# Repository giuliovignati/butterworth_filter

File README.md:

🧈 **Butterworth Low-Pass Filter Design**
 
---

## 📘 Introduction

A **Butterworth filter** is a type of signal processing filter designed to have a frequency response that is as flat as mathematically possible in the passband. Unlike filters that exhibit ripples or irregularities in the passband or stopband, the Butterworth filter provides a smooth and monotonic response, making it ideal for applications that require minimal signal distortion.

This project focuses on the design and analysis of a 7th-order Butterworth low-pass filter based on specific performance requirements, including passband and stopband frequencies, maximum ripple, and minimum attenuation.

---

## 📐 Project Specifications

The specifications provided for this project are summarized in the following table:

| Filter Type |   $f_p$   |   $f_s$   |   $A_{\text{max}}$    |   $A_{\text{min}}$    |  $K$  |
|-------------|-----------|-----------|-----------------------|-----------------------|-------|
| Butterworth | 40 kHz    | 61 kHz    | 2 dB                  | 20 dB                 | 5     |

---

## 🔍 Parameter Calculation and Design Decisions

### 🎛️ Butterworth Filter Poles

The magnitude of the transfer function of a Butterworth filter $T(i\omega)$ is given by:

$|T(i\omega)| = \frac{1}{\sqrt{1 + \varepsilon^2 \left(\frac{\omega}{\omega_p}\right)^{2N}}}$

Where:

- $N$ is the filter order  
- $\varepsilon = \sqrt{10^{A_{\text{max}}/10} - 1} = 0.765$

To ensure a minimum attenuation of $A_{\text{min}}$ in the stopband, the minimum order $N$ required is calculated as:

$A(\omega_s) = 10 \log\left(1 + \varepsilon^2 \left(\frac{\omega_s}{\omega_p}\right)^{2N}\right)$

Solving gives:

$N_{\text{min}} = 7$

Poles lie on a semicircle in the complex plane:

$R = \omega_p \cdot \left(\frac{1}{\varepsilon}\right)^{1/7} = 261.129 \cdot 10^3 \, \text{rad/s}$

**Complex Poles of the Filter:**

| Index       | Pole Expression (in terms of $R$)         |
|-------------|-------------------------------------------|
|  $p_{0,6}$  | $R \cdot (-0.22252 \pm i \cdot 0.97493)$  |
|  $p_{1,5}$  | $R \cdot (-0.62349 \pm i \cdot 0.078183)$ |
|  $p_{2,4}$  | $R \cdot (-0.90097 \pm i \cdot 0.43388)$  |
|    $p_3$    | $-R $                                     |

---

### 🎚️ Pole Frequencies and Quality Factors

Given $p_k = R \cdot (\sigma_k + i\omega_k)$, we derive:

- Resonant frequency:  
  $\omega_0 = R$

- Quality factor:  
  $Q = -\frac{1}{2\sigma}$

**Quality Factors:**

| Poles     | Quality Factor $Q$ |
|-----------|--------------------|
| $p_{0,6}$ | $2.2469$           |
| $p_{1,5}$ | $0.8019$           |
| $p_{2,4}$ | $0.5549$           |

---

## 🔧 Filter Design

### 🧠 Design Choices

The project design involved balancing trade-offs among performance, component count, and sensitivity. The implemented solution includes three smart Sallen-Key stages, a single integrator stage, and an inverting buffer.

An alternative solution aimed at minimizing component usage would have included three Sallen-Key filters, one RC filter, and a non-inverting amplifier stage. This approach would have saved one operational amplifier. However, it was ultimately discarded in favor of a fully active solution, which offers greater versatility and improved performance.

Given the relatively non-stringent specifications, a general-purpose operational amplifier was selected, specifically the *TL072* (and *TL071*).

### 🧩 Component Value Calculation

Following the model of the smart Sallen-Key filter (schematic shown in the following figure), the resistor and capacitor values for each stage are determined according to the following equations:

$\omega_0 = \frac{1}{R \sqrt{C_1 C_2}} \quad$ ; $\quad Q = \frac{1}{2} \sqrt{\frac{C_1}{C_2}}$

Considering the values of $Q$ and $\omega_0$ obtained, and choosing discrete resistor and capacitor values that best approximate the theoretical values, the following values were obtained:

| Component | S-K 1 | S-K 2 | S-K 3 |
| --- | --- | --- | --- |
| $R [k\Omega]$ | $5.1$ | $7.5$ | $7.5$ |
| $C_1 [pF]$ | $820$ | $820$ | $2.2 \cdot 10^3$ |
| $C_2 [pF]$ | $680$ | $330$ | $100$ |
| $Q$ | $0.5491$ | $0.7882$ | $2.3452$ |
| $\omega_0 [krad/s]$ | $262.6$ | $256.3$ | $284.3$ |

For the integrator stage (based on the schematic) the following formulas are used:

$$
\omega_0 = \frac{1}{R_2 C}, \quad K = \frac{R_2}{R_1}
$$

The chosen values are: $R_1 = 8.1k\Omega$,  $R_2' = 39k\Omega$,  $R_2'' = 2k\Omega$, and  $C' = C'' = 47pF$. 

For the inverting buffer, the resistor values are $R = 10k\Omega$. Given the simple DC gain specification, all amplification is handled in the single-pole stage. Therefore, it was the only stage where care was taken to use resistor series to closely approximate the ideal gain value, while the capacitor parallel configuration was used primarily for sizing purposes.

Finally, the order of the stages, from input to output, is: integrator, Sallen-Key smart filter with increasing $Q$, and inverting buffer.

An additional note on filter sizing: Initially, different sizing was planned, especially for the first and third Sallen-Key stages. However, upon testing the real filter's performance and considering the numerous non-idealities of the circuit on a breadboard (e.g., parasitic capacitance), the actual values differed significantly from the expected ones (cutting off at around $4kHz$ instead of the target). As a result, an alternative sizing was chosen to better meet the design specifications, aiming to use larger capacitors to reduce parasitic effects.

## Circuit Sensitivity

The sensitivity values across all stages of the circuit are shown in the tables below. It can be observed that, due to the smart Sallen-Key configuration for all two-pole stages, the circuit exhibits excellent sensitivity values, making it highly robust to variations in component values.

### Sallen-Key Stage Sensitivity

| Component | Sensitivity Value |
| --- | --- |
| $S^Q_R$ | 0 |
| $S^Q_{C_1}$ | 0.5 |
| $S^Q_{C_2}$ | -0.5 |
| $S^{\omega_0}_{\{R,C_1,C_2\}}$ | -0.5 |

### Integrator Stage Sensitivity

| Component | Sensitivity Value |
| --- | --- |
| $S^K_{R_1}$ | -1 |
| $S^K_{R_2}$ | 1 |
| $S^{\omega_0}_{\{R_2,C\}}$ | -1 |
| $S^{\omega_0}_{R_1}$ | 0 |

### Inverting Buffer Sensitivity

| Component | Sensitivity Value |
| --- | --- |
| $S^K_{R_1}$ | -1 |
| $S^K_{R_2}$ | 1 |

--- 

## ⚙️ Spice Simulations
#### Schematic used for Spice simulations

### Fourier Domain Analysis

The previous schematic was used to perform the following Montecarlo simulation with $5\%$ tolerance for resistors and $15\%$ tolerance for capacitors, while the values presented in the table below refer to the simulation with exact nominal values. The last row in the table shows the actual frequency at which $A_{min} = 2dB$ is satisfied, which occurs with a $0.5kHz$ offset.

At this point, it is essential to observe that at $61kHz$, the attenuation is much smaller compared to the designed value ($\approx -6dB$). This discrepancy is due to the effect of additional poles in the circuit, probably caused by the non-idealities of the operational amplifiers. This effect can be directly observed in the simulation with nominal values by evaluating the phase Bode plot. In addition to the contribution from the 7 poles coinciding around $40kHz$, which would lead to a total phase shift of $630^\circ$, an additional phase shift is visible beyond $0.5MHz$, suggesting the presence of extra poles. It is worth noting that this behavior could have allowed us to achieve a solution that fully met the design specifications, for example, by simply shifting the cutoff frequency $\omega_0$ of the stages further ahead. However, we chose not to implement this solution in order to remain consistent with the theoretical models, while still obtaining valid results with this configuration.

#### Bode Diagram Simulation Values (Nominal Values)

| Frequency | $V_{out}/V_{in}$ [dB] | $V_{out}/V_{in}$ [V] |
| --- | --- | --- |
| $DC (1Hz)$ | $13.98$ | $5$ |
| $40kHz$ | $11.80$ | $3.89$ |
| $61kHz$ | $-8.67$ | $0.37$ |
| $39.5kHz$ | $11.98$ | $3.97$ |

#### Montecarlo simulation:

#### Montecarlo simulation with cutoff zoom:

#### Nominal frequency analysis:

### 🕒 Time Domain Analysis

The time domain simulations of the filter at the relevant frequencies are shown in the following graphs. The peak values presented are entirely consistent with those calculated previously.

#### 1Hz Simulation

#### 40Hz Simulation

#### 61Hz Simulation

### Notes on Non-Ideal Component Sizing

As previously mentioned, initial alternative sizing options were proposed using real measured values, which leveraged component imprecision to achieve more accurate $Q$ and $\omega_0$ values for each stage (as shown in the following schematic). This approach led to simulations that fully satisfied the design specifications (see following table).

However, this sizing strategy was ultimately discarded because the component values deviated significantly from their nominal counterparts. This made the solution impractical for large-scale implementation, as it relied on the non-ideal behavior of resistors and capacitors. Additionally, while simulations using nominal values were still somewhat acceptable, the use of very small capacitors had significant effects in the real circuit implementation, resulting in performance that deviated substantially from the design specifications.

#### Bode Diagram Simulation Values (Alternative Real Sizing)

| Frequency | $V_{out}/V_{in}$ [dB] | $V_{out}/V_{in}$ [V] |
| --- | --- | --- |
| $DC (1Hz)$ | $14.074$ | $5.05$ |
| $40kHz$ | $12.36$ | $4.15$ |
| $61kHz$ | $-10.12$ | $0.31$ |

#### Filter Schematic with alternative real values 

## Physical Implementation of the Circuit and Experimental Measurements

The following oscilloscope screenshots display the input (Channel 1) and the output (Channel 2) of the filter. Compared to the ideal simulations previously shown in Table, non-idealities in the circuit and deviations from nominal component values led to a shift of approximately $0.7kHz$ in the actual cutoff frequency.

#### 100Hz Measurement

#### 40kHz Measurement

#### 61kHz Measurement

The following table presents the current measurements for each operational amplifier and estimates of power consumption. It was observed that the current draw remains constant throughout the input frequency range.

#### Measured Voltages at Key Frequencies

|       | $V_{in}$ [V] | $V_{out}$ [V] |
|-------|--------------|---------------|
| $DC (1Hz)$ | $1.03$ | $5.2$ |
| $40kHz$    | $1.03$ | $3.58$ |
| $61kHz$    | $1.03$ | $0.314$ |
| $38.8kHz$  | $1.03$ | $3.96$ |

#### Current and Power Dissipation (Power Supply: $\pm12V$)

| Component       | Current [$mA$] | Power Dissipated [$mW$] |
|-----------------|----------------|--------------------------|
| $TL072^{'}$     | $3.972$         | $95.33$                  |
| $TL072^{''}$    | $1.769$         | $42.26$                  |
| $TL071$         | $1.319$         | $31.66$                  |

## ⚡ PCB Circuit Schematic

To ensure project completeness and replicability, the circuit schematic was transposed into KiCad, an open-source suite for electrical schematic and PCB design.

The schematic was structured using a block-division approach to enhance clarity. Input, output, and power blocks were specifically highlighted. For completeness, unconnected pins, power lines, and the selected mounting holes were marked and properly grounded.

Given the schematic's simplicity, we opted for a 2-layer board layout: the top layer is dedicated to signal lines, while the bottom layer features a ground plane and power traces for the op-amps. This setup enhances reference stability.

A significant design decision was the selection of **footprints** for each component — i.e., standardized physical packages. With no strict space constraints, we selected **TH (Through-Hole)** packages. Despite being bulkier than SMD (Surface Mount Device) equivalents, TH components are easier to source and solder manually.

- **Resistors**: 1/4W, metal film
- **Capacitors**: Ceramic, 50V tolerance

#### Selected Footprint Dimensions

| Component   | Length [mm] | Diameter [mm] | Pitch [mm] |
|-------------|--------------|----------------|-------------|
| Resistor    | 6.3          | 2.5            | 10.16       |
| Capacitor   | 4.7          | 2.5            | 5.0         |

To allow for easy substitution of op-amps, we used **DIP8 sockets** (Dual In-line Package, 8 pins, 7.62mm nominal width), enabling insertion/removal without soldering.

Peripheral connections are handled via **screw terminals (KF301)**. These meet project specs comfortably:

- **Pitch**: 5.08mm  
- **Max Current**: 13.5A  
- **Max Voltage**: 250V  
- **Wire Size Range**: 26AWG – 16AWG  

Before routing, trace widths were dimensioned using KiCad's **Track Width Calculator**, based on max current, trace length, and temperature rise:

- **Signal traces**: 0.35mm  
- **Power traces**: 0.4mm  

These values fully satisfy design constraints.

### ✅ Additional Design Steps

- **ERC (Electrical Rules Check)** and **DRC (Design Rules Check)** were performed in KiCad.
- Manufacturer constraints (e.g., JLC PCB) were input for validation.
- Front and back **Silkscreen labels** were added for reference values.
- KiCad's **3D Viewer** was used to preview the assembled board, verify component spacing, and inspect label positioning before production.

#### KiCad Schematic

#### KiCad PCB editor view

#### PCB view (front side) from 3d viewer

#### PCB view (back side) from 3d viewer

#### PCB view with selected 3d models from 3d viewer

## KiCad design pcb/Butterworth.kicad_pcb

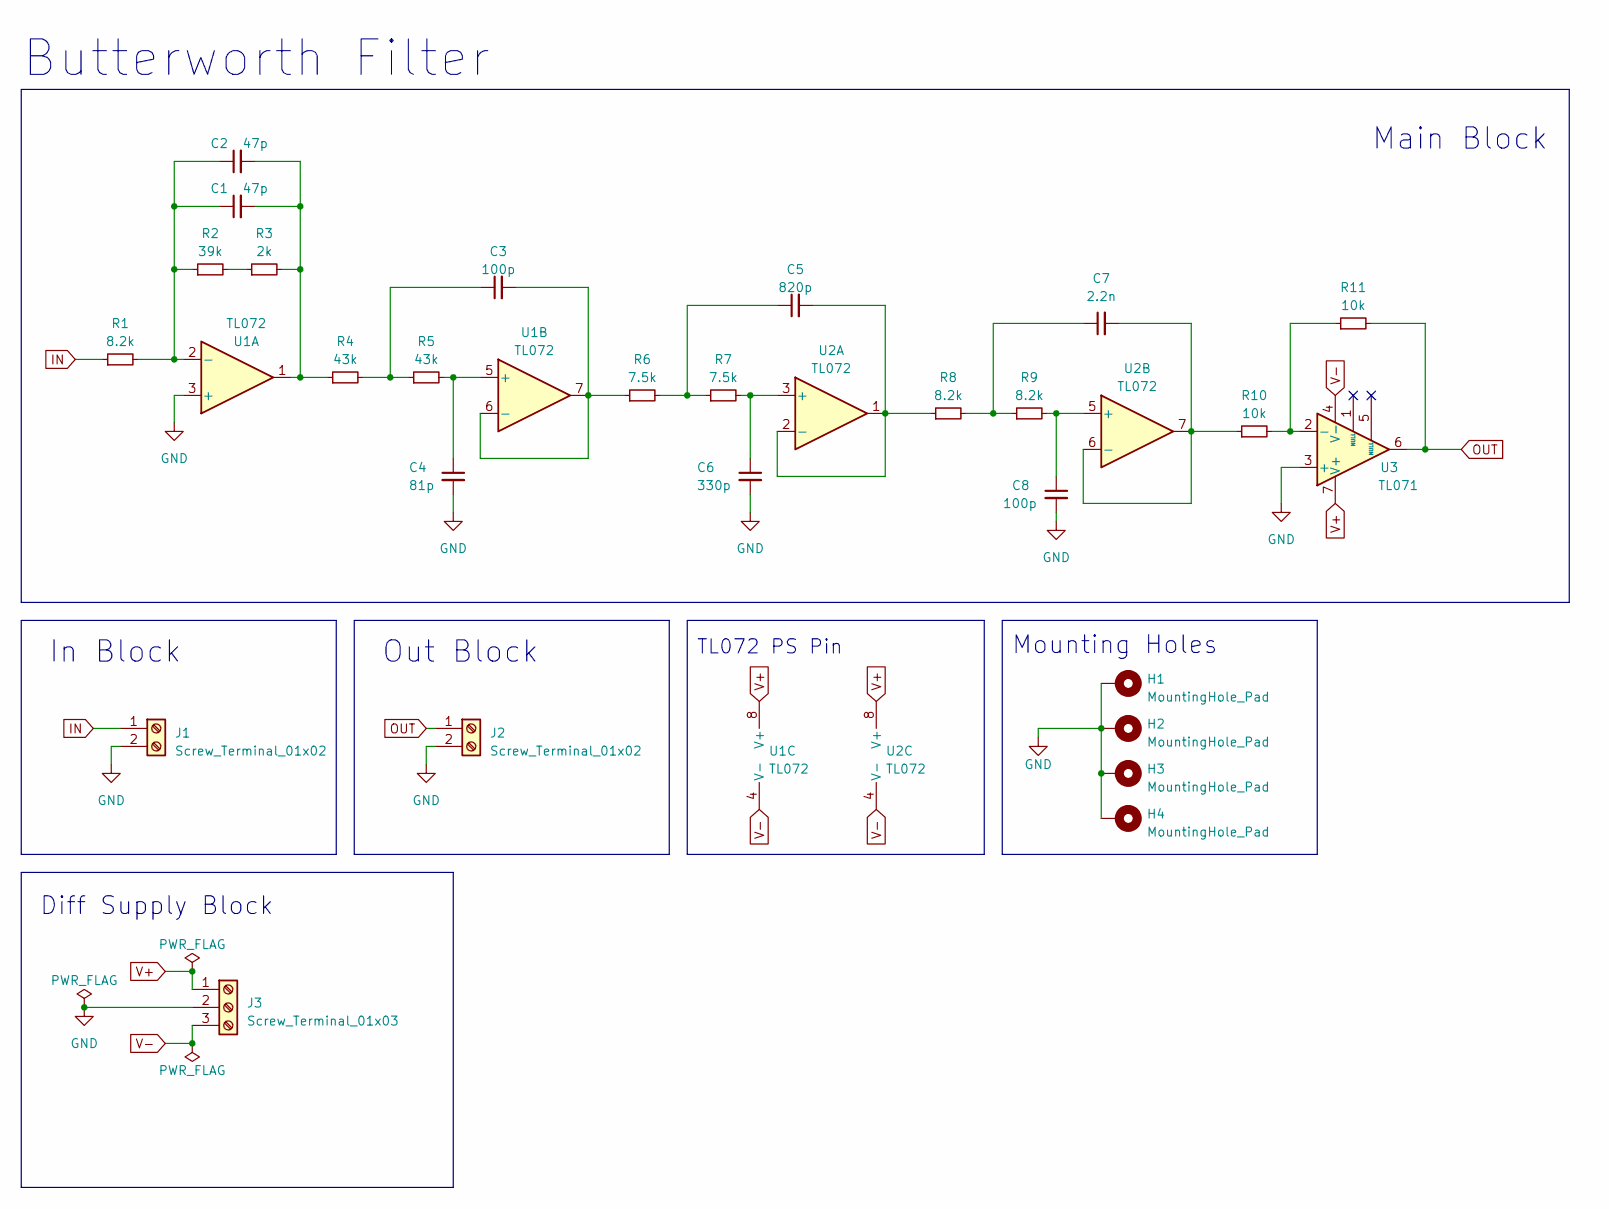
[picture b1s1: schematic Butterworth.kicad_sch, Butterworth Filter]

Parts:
C1, C2: 47p; C_Disc_D4.7mm_W2.5mm_P5.00mm
C3, C8: 100p; C_Disc_D4.7mm_W2.5mm_P5.00mm
C4: 81p; C_Disc_D4.7mm_W2.5mm_P5.00mm
C5: 820p; C_Disc_D4.7mm_W2.5mm_P5.00mm
C6: 330p; C_Disc_D4.7mm_W2.5mm_P5.00mm
C7: 2.2n; C_Disc_D4.7mm_W2.5mm_P5.00mm
H1, H2, H3, H4: MountingHole_Pad; MountingHole_4.3mm_M4_Pad_Via
J1, J2: Screw_Terminal_01x02; TerminalBlock_bornier-2_P5.08mm
J3: Screw_Terminal_01x03; TerminalBlock_bornier-3_P5.08mm
R1, R8, R9: 8.2k; R_Axial_DIN0207_L6.3mm_D2.5mm_P10.16mm_Horizontal
R2: 39k; R_Axial_DIN0207_L6.3mm_D2.5mm_P10.16mm_Horizontal
R3: 2k; R_Axial_DIN0207_L6.3mm_D2.5mm_P10.16mm_Horizontal
R4, R5: 43k; R_Axial_DIN0207_L6.3mm_D2.5mm_P10.16mm_Horizontal
R6, R7: 7.5k; R_Axial_DIN0207_L6.3mm_D2.5mm_P10.16mm_Horizontal
R10, R11: 10k; R_Axial_DIN0207_L6.3mm_D2.5mm_P10.16mm_Horizontal
U1, U2: TL072; DIP-8_W7.62mm_Socket
U3: TL071; DIP-8_W7.62mm_Socket

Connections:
GND: C4.2, C6.2, C8.2, H1.1, H2.1, H3.1, H4.1, J1.2, J2.2, J3.2, U1.3 (+), U3.3 (+)
IN: J1.1, R1.1
unnamed: C1.2, C2.2, R3.2, R4.1, U1.1
unnamed: C3.1, R4.2, R5.1
unnamed: C5.1, R6.2, R7.1
unnamed: C7.1, R8.2, R9.1
unnamed: R2.2, R3.1
unnamed: C1.1, C2.1, R1.2, R2.1, U1.2 (-)
unnamed: C4.1, R5.2, U1.5 (+)
unnamed: C3.2, R6.1, U1.6 (-), U1.7
unnamed: C6.1, R7.2, U2.3 (+)
unnamed: C5.2, R8.1, U2.1, U2.2 (-)
unnamed: C8.1, R9.2, U2.5 (+)
unnamed: C7.2, R10.1, U2.6 (-), U2.7
unnamed: R10.2, R11.1, U3.2 (-)
OUT: J2.1, R11.2, U3.6
V+: J3.1, U1.8 (V+), U2.8 (V+), U3.7 (V+)
V-: J3.3, U1.4 (V-), U2.4 (V-), U3.4 (V-)

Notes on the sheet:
Main Block
Mounting Holes
Out Block
TL072 PS Pin
Butterworth Filter
In Block
Diff Supply Block

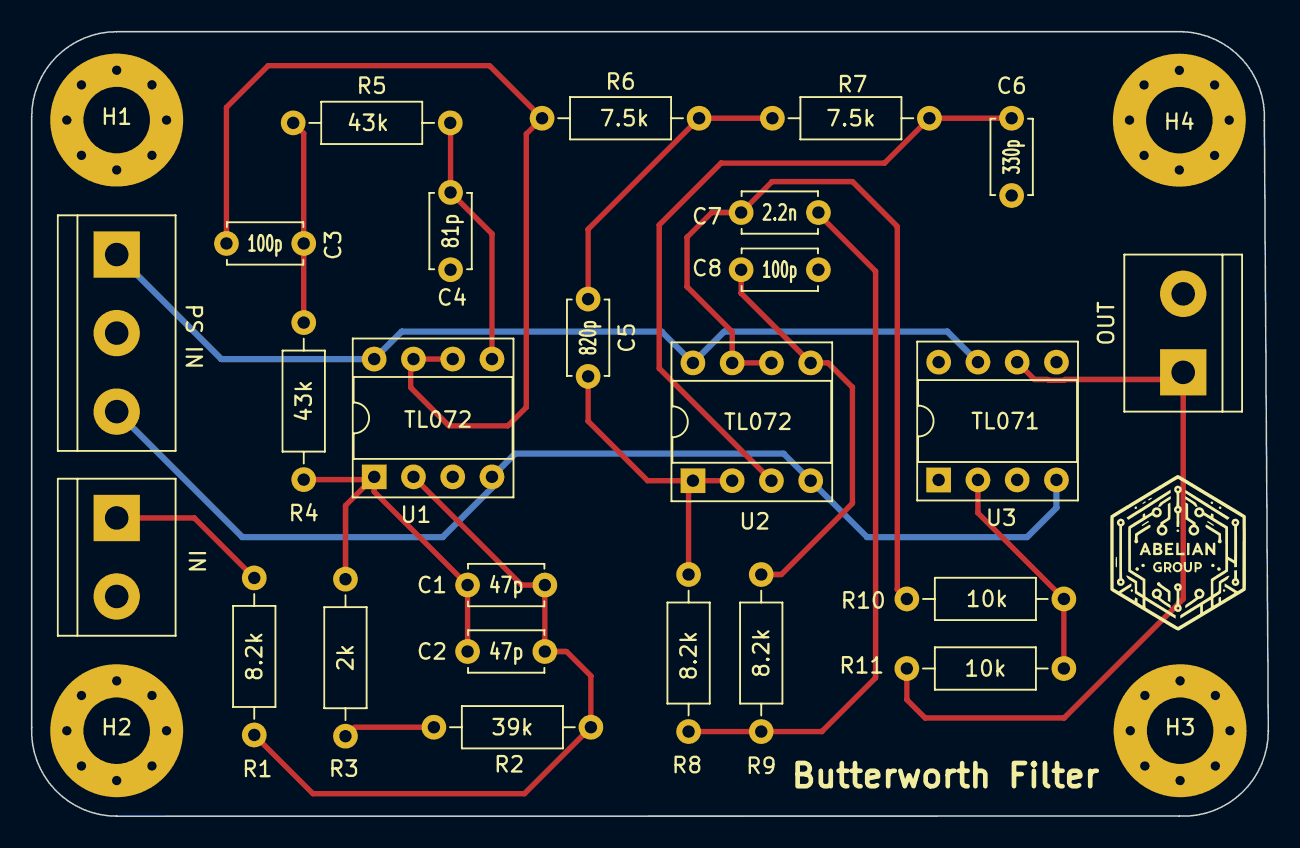
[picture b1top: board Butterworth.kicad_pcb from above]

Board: 2 copper layers, 80.0 x 50.8 mm, 29 parts (0 on the bottom side), 18 nets.

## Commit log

2025-04-23 KiCad PCB files and gerbers
2025-04-25 Simulations with real values
